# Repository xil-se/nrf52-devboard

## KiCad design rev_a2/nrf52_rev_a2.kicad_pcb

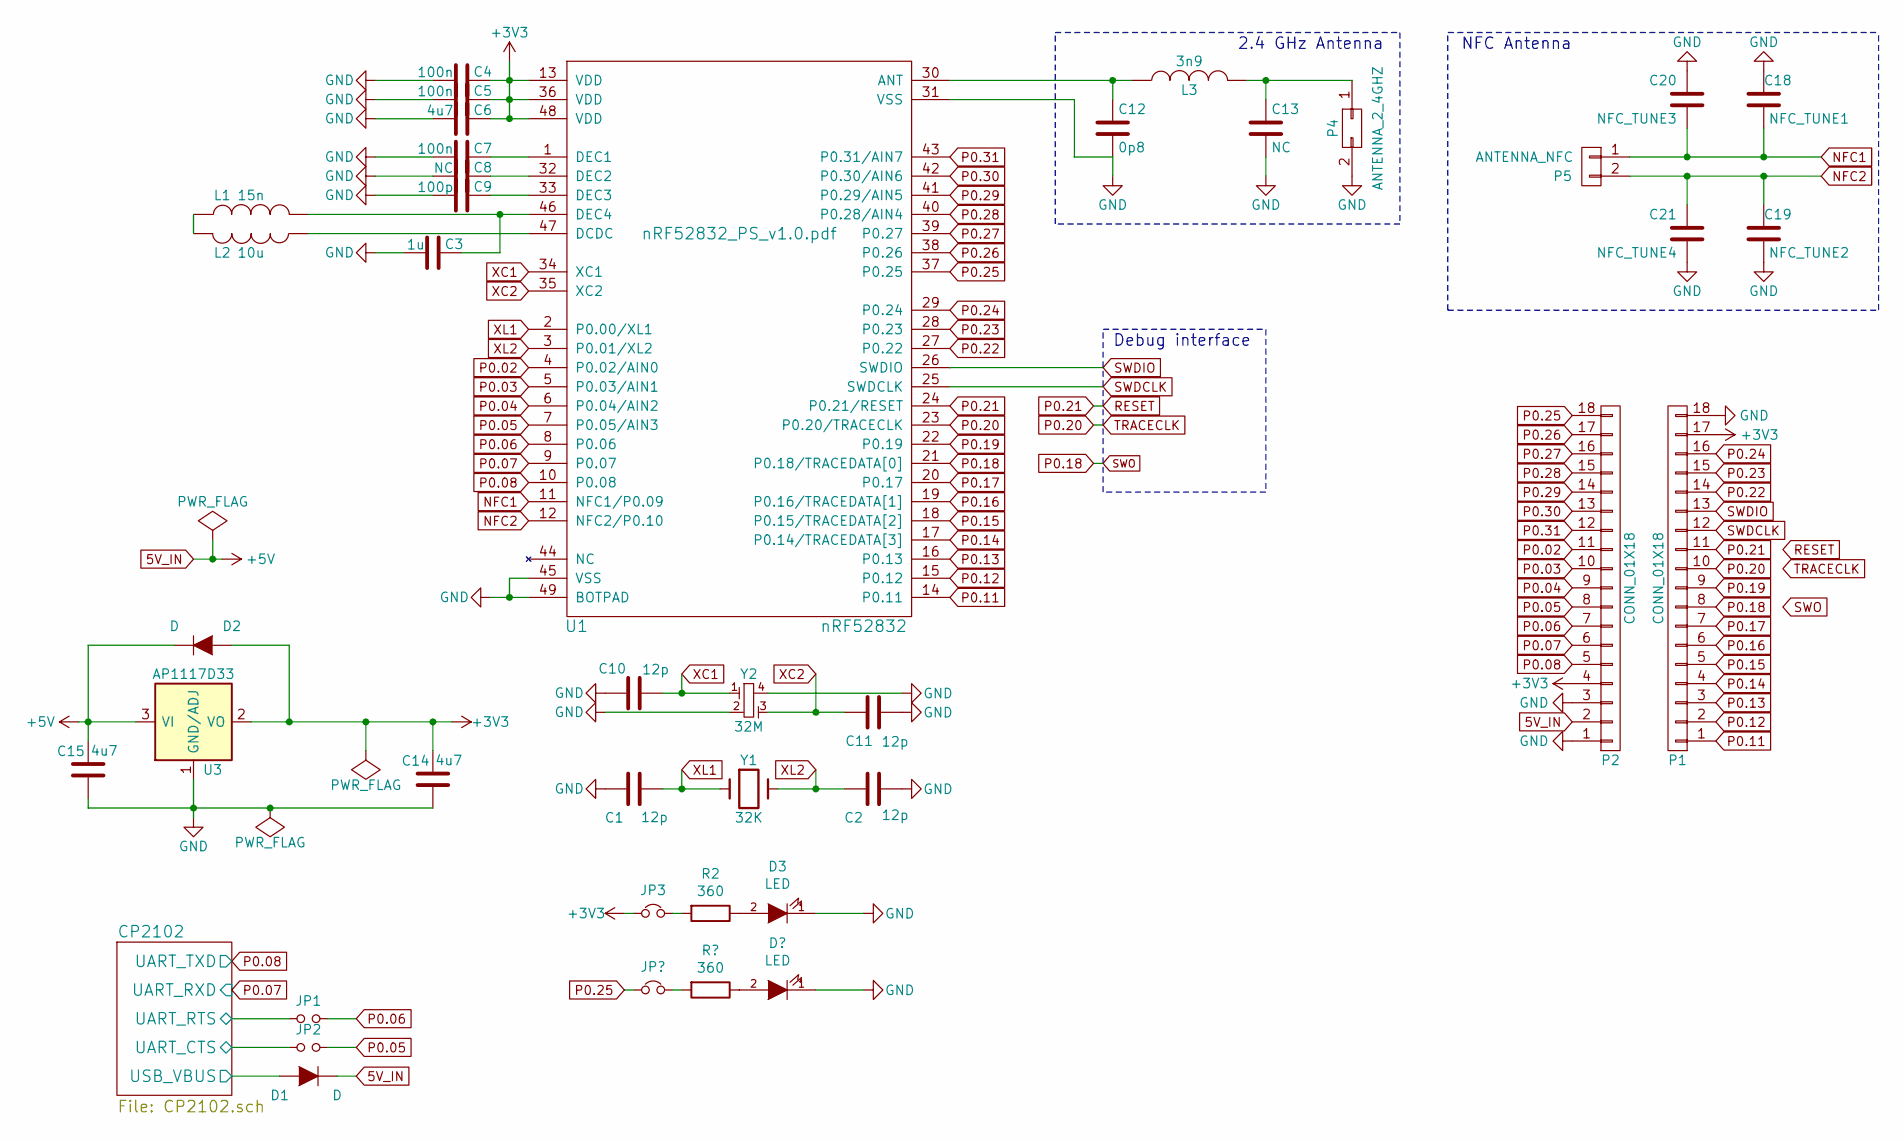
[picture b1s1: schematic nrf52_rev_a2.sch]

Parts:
C1, C2, C10, C11: 12p; 0603_CAP
C3: 1u; 0603_CAP
C4, C5, C7: 100n; 0603_CAP
C6, C14, C15: 4u7; 0603_CAP
C8, C13: NC; 0603_CAP
C9: 100p; 0603_CAP
C12: 0p8; 0603_CAP
C18: NFC_TUNE1; 0603_CAP
C19: NFC_TUNE2; 0603_CAP
C20: NFC_TUNE3; 0603_CAP
C21: NFC_TUNE4; 0603_CAP
D1, D2: D; SOD-323
D3: LED; 0603_LED
JP1, JP2: Jumper_NO_Small; SolderBridgeLarge
JP3: Jumper_NC_Small; SolderBridgeLarge_NC
L1: 15n; 0603_IND
L2: 10u; 0603_IND
L3: 3n9; 0603_IND
P1, P2: CONN_01X18; Pin_Header_Straight_1x18
P4: ANTENNA_2_4GHZ; ti-an043-antenna
P5: ANTENNA_NFC; nfc_30x18_w05mm_s06mm
R2: 360; 0603_RES
U1: nRF52832; QFN-48_6X6MM_BOTPAD
U3: AP1117D33; SOT-223
Y1: 32K; 32X15MM_2PIN_CRYSTAL
Y2: 32M; 20X16MM_4PIN_CRYSTAL

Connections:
5V_IN: C15.2, D1.1 (K), D2.1 (K), P2.2, U3.3 (VI)
+3V3: C4.1, C5.1, C6.1, C14.2, D2.2 (A), JP3.1, P1.17, P2.4, U1.13 (VDD), U1.36 (VDD), U1.48 (VDD), U3.2 (VO); also elsewhere on the board
/CP2102/UART_CTS: JP2.1; also elsewhere on the board
/CP2102/UART_RTS: JP1.1; also elsewhere on the board
/CP2102/USB_VBUS: D1.2 (A); also elsewhere on the board
GND: C1.1, C2.2, C3.2, C4.2, C5.2, C6.2, C7.2, C8.2, C9.2, C10.2, C11.1, C12.2, C13.2, C14.1, C15.1, C18.1, C19.2, C20.1, C21.2, D3.1 (K), P1.18, P2.1, P2.3, P4.2, U1.31 (VSS), U1.45 (VSS), U1.49 (BOTPAD), U3.1 (GND/ADJ), Y2.2, Y2.4; also elsewhere on the board
NFC1: C18.2, C20.2, P5.1, U1.11 (NFC1/P0.09)
NFC2: C19.1, C21.1, P5.2, U1.12 (NFC2/P0.10)
unnamed: C3.1, L1.2, U1.46 (DEC4)
unnamed: C7.1, U1.1 (DEC1)
unnamed: C8.1, U1.32 (DEC2)
unnamed: C9.1, U1.33 (DEC3)
unnamed: C12.1, L3.1, U1.30 (ANT)
unnamed: C13.1, L3.2, P4.1
unnamed: D3.2 (A), R2.1
unnamed: JP3.2, R2.2
unnamed: L1.1, L2.2
unnamed: L2.1, U1.47 (DCDC)
P0.02: P2.11, U1.4 (P0.02/AIN0)
P0.03: P2.10, U1.5 (P0.03/AIN1)
P0.04: P2.9, U1.6 (P0.04/AIN2)
P0.05: JP2.2, P2.8, U1.7 (P0.05/AIN3)
P0.06: JP1.2, P2.7, U1.8 (P0.06)
P0.07: P2.6, U1.9 (P0.07); also elsewhere on the board
P0.08: P2.5, U1.10 (P0.08); also elsewhere on the board
P0.11: P1.1, U1.14 (P0.11)
P0.12: P1.2, U1.15 (P0.12)
P0.13: P1.3, U1.16 (P0.13)
P0.14: P1.4, U1.17 (P0.14/TRACEDATA[3])
P0.15: P1.5, U1.18 (P0.15/TRACEDATA[2])
P0.16: P1.6, U1.19 (P0.16/TRACEDATA[1])
P0.17: P1.7, U1.20 (P0.17)
P0.18: P1.8, U1.21 (P0.18/TRACEDATA[0])
P0.19: P1.9, U1.22 (P0.19)
P0.20: P1.10, U1.23 (P0.20/TRACECLK)
P0.21: P1.11, U1.24 (P0.21/RESET)
P0.22: P1.14, U1.27 (P0.22)
P0.23: P1.15, U1.28 (P0.23)
P0.24: P1.16, U1.29 (P0.24)
P0.25: P2.18, U1.37 (P0.25); also elsewhere on the board
P0.26: P2.17, U1.38 (P0.26)
P0.27: P2.16, U1.39 (P0.27)
P0.28: P2.15, U1.40 (P0.28/AIN4)
P0.29: P2.14, U1.41 (P0.29/AIN5)
P0.30: P2.13, U1.42 (P0.30/AIN6)
P0.31: P2.12, U1.43 (P0.31/AIN7)
SWDCLK: P1.12, U1.25 (SWDCLK)
SWDIO: P1.13, U1.26 (SWDIO)
XC1: C10.1, U1.34 (XC1), Y2.1
XC2: C11.2, U1.35 (XC2), Y2.3
XL1: C1.2, U1.2 (P0.00/XL1), Y1.1
XL2: C2.1, U1.3 (P0.01/XL2), Y1.2

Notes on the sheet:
Debug interface
NFC Antenna
2.4 GHz Antenna

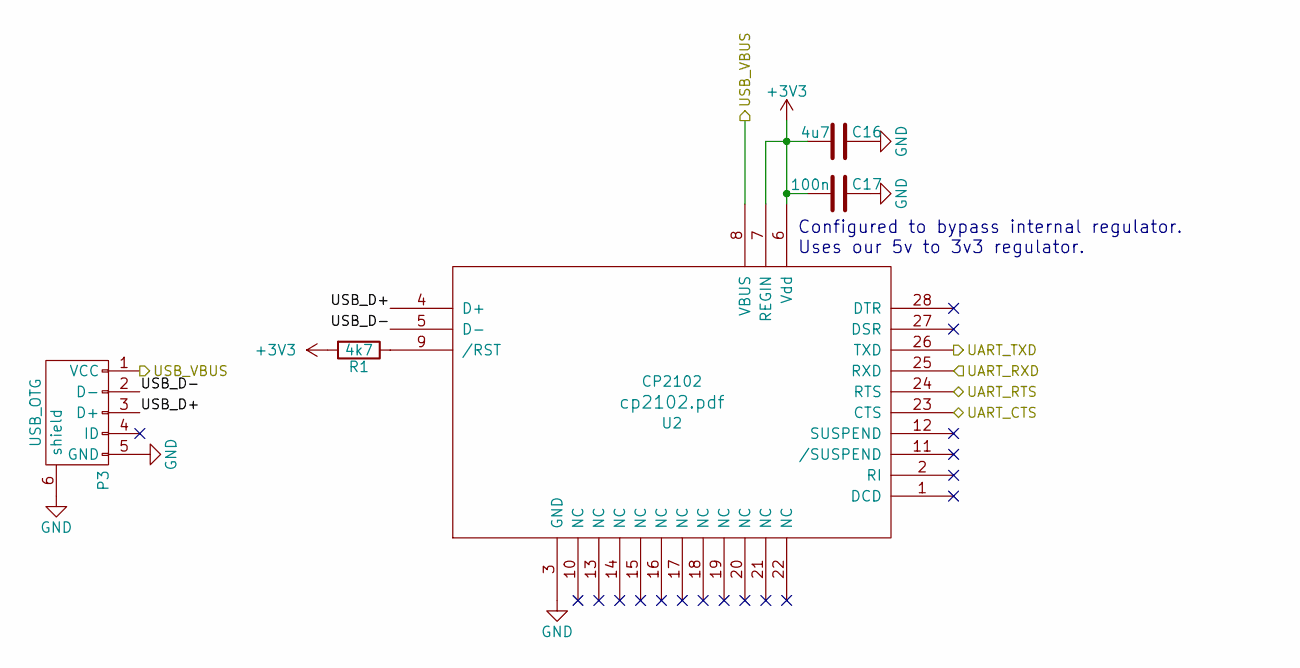
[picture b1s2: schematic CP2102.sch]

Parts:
C16: 4u7; 0603_CAP
C17: 100n; 0603_CAP
P3: USB_OTG; USB_Micro-B
R1: 4k7; 0603_RES
U2: CP2102; QFN-28-1EP_5x5mm_Pitch0.5mm

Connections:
+3V3: C16.2, C17.2, R1.2, U2.6 (Vdd), U2.7 (REGIN); also elsewhere on the board
/CP2102/UART_CTS: U2.23 (CTS); also elsewhere on the board
/CP2102/UART_RTS: U2.24 (RTS); also elsewhere on the board
/CP2102/USB_D+: P3.3 (D+), U2.4 (D+)
/CP2102/USB_D-: P3.2 (D-), U2.5 (D-)
/CP2102/USB_VBUS: P3.1 (VCC), U2.8 (VBUS); also elsewhere on the board
GND: C16.1, C17.1, P3.5 (GND), P3.6 (shield), U2.3 (GND); also elsewhere on the board
unnamed: R1.1, U2.9 (/RST)
P0.07: U2.25 (RXD); also elsewhere on the board
P0.08: U2.26 (TXD); also elsewhere on the board

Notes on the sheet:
Configured to bypass internal regulator. Uses our 5v to 3v3 regulator.

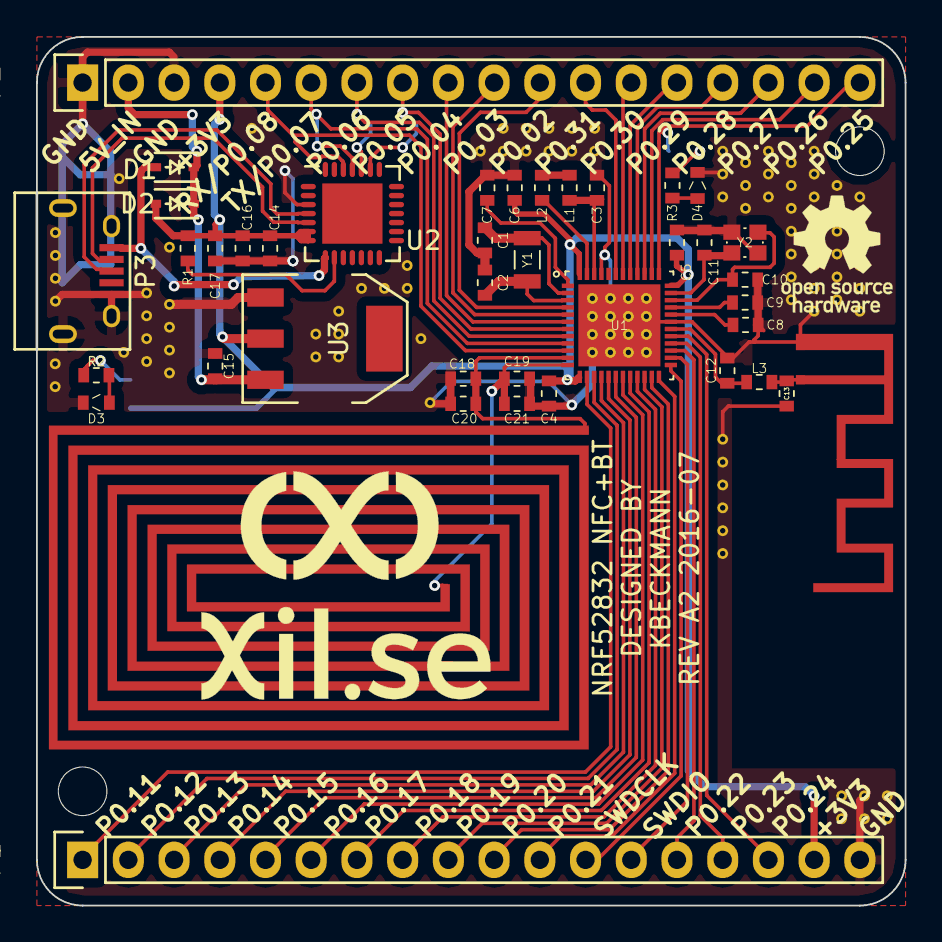
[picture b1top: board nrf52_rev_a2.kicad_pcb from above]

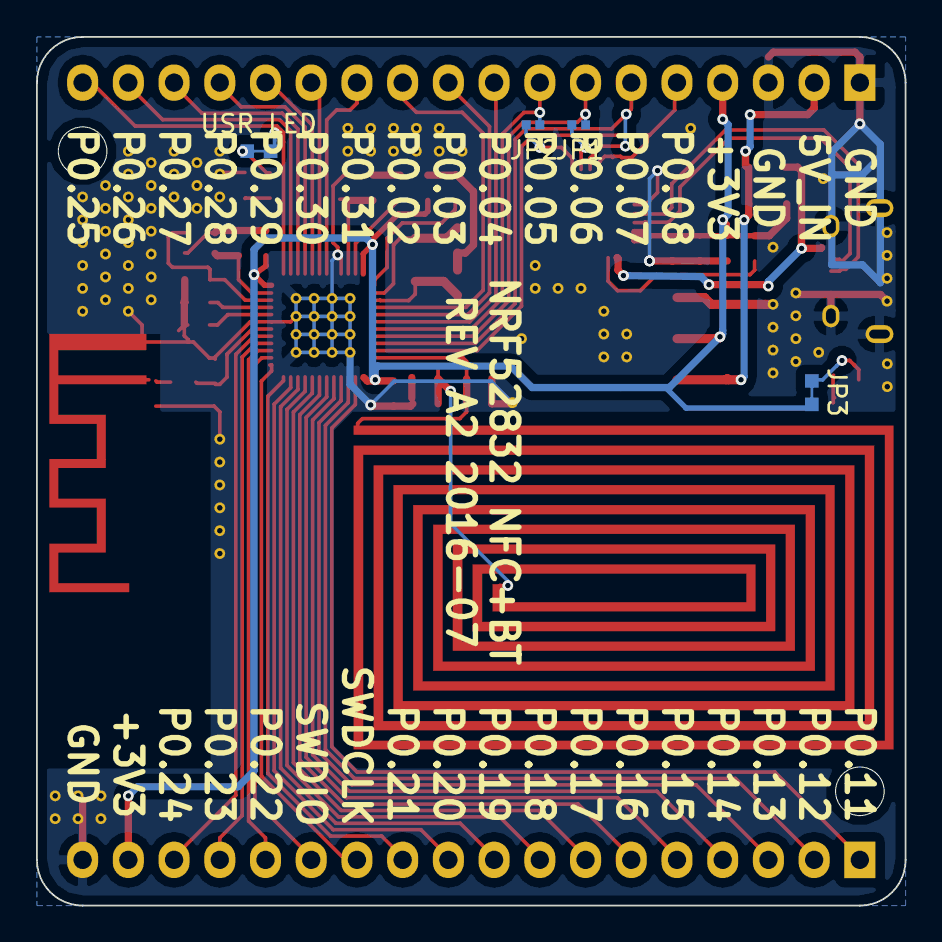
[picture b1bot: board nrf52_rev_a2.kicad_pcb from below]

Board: 2 copper layers, 48.3 x 48.3 mm, 45 parts (4 on the bottom side), 57 nets.

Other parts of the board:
D4: LED; 0603_LED
R3: 360; 0603_RES
USR_LED: Jumper_NC_Small; SolderBridgeLarge_NC

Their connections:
GND: D4.1; also elsewhere on the board
unnamed: D4.2, R3.1
unnamed: R3.2, USR_LED.2
P0.25: USR_LED.1; also elsewhere on the board

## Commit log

2016-06-12 All the stuff
2016-06-12 remove bak
2016-06-12 Wiiip
2016-06-12 Wörk wörk
2016-06-12 wipwipwip
2016-06-16 Made the design great again
2016-06-16 Added logo etc
2016-06-16 Almost done
2016-06-16 Add missing files
2016-06-17 WIP IT! Finally somethings nice yo.
2016-06-18 Make it nicer
2016-06-18 Add 3d files
2016-06-18 Adjust usb port
2016-06-18 cleanup
2016-06-18 Added datasheets
2016-06-18 Fixed antenna caps
2016-06-18 more nfc space
2016-06-18 uhh, hope this works
2016-06-18 tidy up
2016-06-18 Gitignore
2016-06-18 Added NFC antenna
2016-06-18 soon going gold
2016-06-18 assets
2016-06-18 changed diode connections
2016-06-18 text
2016-06-19 Added some space between tracks
2016-06-21 Changed to GND on both sides and added lots of vias
2016-06-22 minor tweaks
2016-06-22 final touches
2016-06-23 Adjusted component labels
2016-06-23 Add files
2016-06-23 Added gnd tracks from usb connector
2016-06-24 Add nfc antenna document
2016-06-24 Found the xls as well
2016-06-24 more nfc info
2016-06-24 Last changes to rev_a1
2016-07-19 Add rev_a2
